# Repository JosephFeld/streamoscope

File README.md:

# Streamoscope
The Streamoscope is a USB-3 data acquisition system designed for low-field MRI, but could be more generally used. It streams two channels at 60 megasamples per second with 14-bit precision and costs around $300 in parts. It can read in data with low latency and the limit of how much can be read is only limited by the RAM on your computer!

It reads in 8 channels of data from the [AFE5812 analog front end chip](https://www.ti.com/product/AFE5812) into an [Alchitry Au FPGA board](https://www.sparkfun.com/products/16527), which feeds it into an [FT601 FIFO-to-USB-3 Bridge](https://ftdichip.com/products/ft601q-b/) which can be read into [Python](https://www.python.org/). Due to bandwidth constraints of the FT601, it only streams two channels. However, more could be streamed with a modified FPGA design that decimates the signals or decreases their precision.

What follows are guides on how to access the various components of the system. To summarize them:

* PCB design files from KiCad
* Python code for reading in data from the FT601
* Teensy code for configuring the AFE5812
* How to configure the Alchitry Au FPGA
* A Vivado project for the FPGA design

# PCB

The PCB design was done in [KiCad 8.0](https://www.kicad.org/) and can be found in ```streamoscope/hardware/kicad_design```. There are custom footprints used, which are accessible in this [library](https://github.com/JosephFeld/Handheld-MRI-Parts). Special thanks to [Lopfi for making the Alchitry Au footprint](https://github.com/Lopfi/alchitry-element-kicad).

# Python Setup

Streamoscope data can be read into Python, and this guide will walk through setting up the Jupyter Notebook example. This uses Python 3, which can be downloaded [here](https://www.python.org/downloads/).

## Installing libusb

First, we need to install [libusb](https://libusb.info/).

### MacOS

On MacOS, run these commands in the terminal: 
```
brew install libusb
sudo ln -s /opt/homebrew/lib/libusb-1.0.0.dylib /usr/local/lib/libusb.dylib
```

### Windows

On Windows, download the latest libusb Windows binaries [here](https://libusb.info/) under Downloads>Latest Windows Binaries.

Unzip the file and choose a version corresponding to your operating system. A good default is the newest Visual Studio folder VS2022. Choose the subfolder corresponding to your operating system, either 32 or 64 for 32-bit or 64-bit systems, respectively. Copy ```libusb-1.0.dll``` in the ```dll``` folder into ```C:/Windows/System32```, which will require admin approval. ```libusb-1.0.dll``` can also be placed into the same directory as the python script, ```streamoscope/software/python_reading``` for this example.

The FT601 on the Streamoscope may have the incorrect drivers. To fix this, install [Zadig](https://zadig.akeo.ie/) and run it.

* Select Options\>List All Devices
* Select FTDI SuperSpeed-FIFO Bridge (Interface 0)
* Use the arrows on the right to select libusbK as the new driver.

Here's what it should look like:

* Click "Replace Driver"

## Python dependencies

Then install the Python dependencies

```
pip install libusb, pyusb, matplotlib, numpy, scipy, jupyter
```

## Jupyter Notebook Setup

In the terminal, cd into ```streamoscope/software/python_reading``` and run this command to start up the Jupyter Notebook:

```jupyter notebook .\spin_echo_reader.ipynb```

# Teensy Setup

The Streamoscope uses a Teensy 4.1 microcontroller to configure the AFE5812 Analog Front End and ADC. The software for programming the Teensy can be found [here](https://www.pjrc.com/teensy/td_download.html).

To plug the Teensy into the Streamoscope, connect these pins:

| Streamoscope Pin | Teensy Pin |
| ---------------- | ---------- |
| ADC_RESET        | 3          |      
| MISO             | 39         |
| MOSI             | 26         |
| SCLK             | 27         |
| CS_AFE           | 38         |

And program the Teensy using the code in ```streamoscope\software\teensy_4_1_afe5812_config\teensy_4_1_afe5812_config.ino```. Every time the Teensy powers up, it reconfigures the AFE5812. 

# Configuring Alchitry Au

The Alchitry Au can be programmed using [Alchitry Loader](https://alchitry.com/alchitry-labs/) with the bitstreams found in ```streamoscope/fpga_configurations/```. It is also compatible with [openFPGALoader](https://github.com/trabucayre/openFPGALoader).

There is also a JTAG port broken out which can be used with JTAG programmers like [this](https://digilent.com/shop/jtag-hs3-programming-cable/), which can enable use of the Vivado ILA.

Here are descriptions of each bitstream:

| Filename | Description |
| ---------------- | ---------- |
| teensy_triggered.bit  | Streams channels 1 and 3 with data validity set by GPIO_0 (active high). This is useful for individual spin echoes. |      
| teensy_triggered_with_500ms_trigger_extension.bit | Streams channels 1 and 3 with data validity set by GPIO_0 (active high). Validity lasts an extra 500 milliseconds after GPIO_0 goes low. This is useful for fast imaging sequences. |

# Vivado Project Setup
The FPGA design was made in [Vivado 2023.2](https://www.xilinx.com/support/download/index.html/content/xilinx/en/downloadNav/vivado-design-tools/2023-2.html). It is only necessary to use this if you need to modify the HDL on the FPGA since There is already a provided FPGA configuration.

Open the Vivado GUI, go to the tcl console on the bottom, and cd into the ```streamoscope/hdl/Streamoscope/``` directory. Then run this command:

```
source Streamoscope.tcl
```

Then wait for a bit while the project configures. It will open up the new Streamoscope project. Then in the new project's tcl console, generate the modified ADC LVDS IP with these commands:

```
cd ../ADC-lvds-main/ip
source adc_lvds_ip.tcl
```

Then run this command in the Streamoscope tcl console to update the IP catalog:

```
update_ip_catalog -rebuild
```

If you're running on a version after 2023.2, you may need to update the IP versions. You can do that by navigating to Reports>Report IP Status. In the menu that pops up, select Upgrade Selected.

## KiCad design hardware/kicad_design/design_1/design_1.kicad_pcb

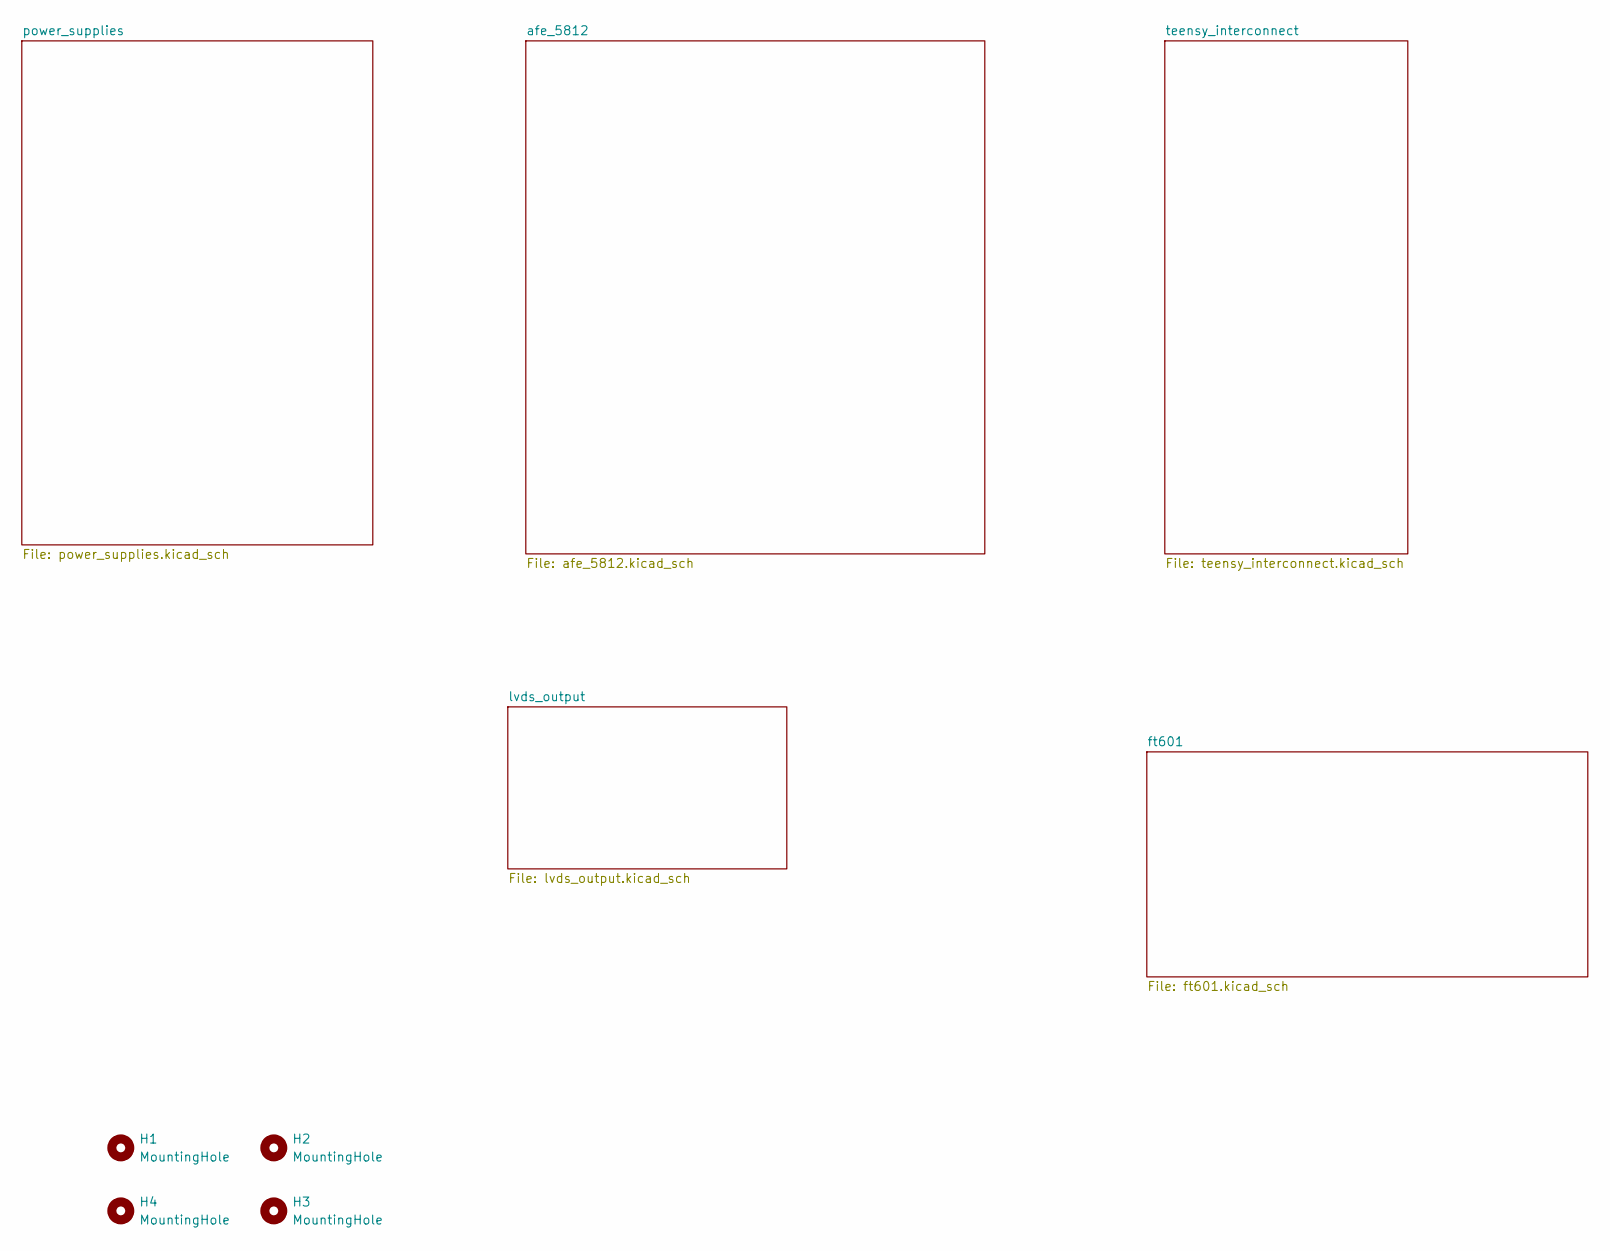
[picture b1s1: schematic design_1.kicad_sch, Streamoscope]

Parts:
H1, H2, H3, H4: MountingHole; MountingHole_2.2mm_M2

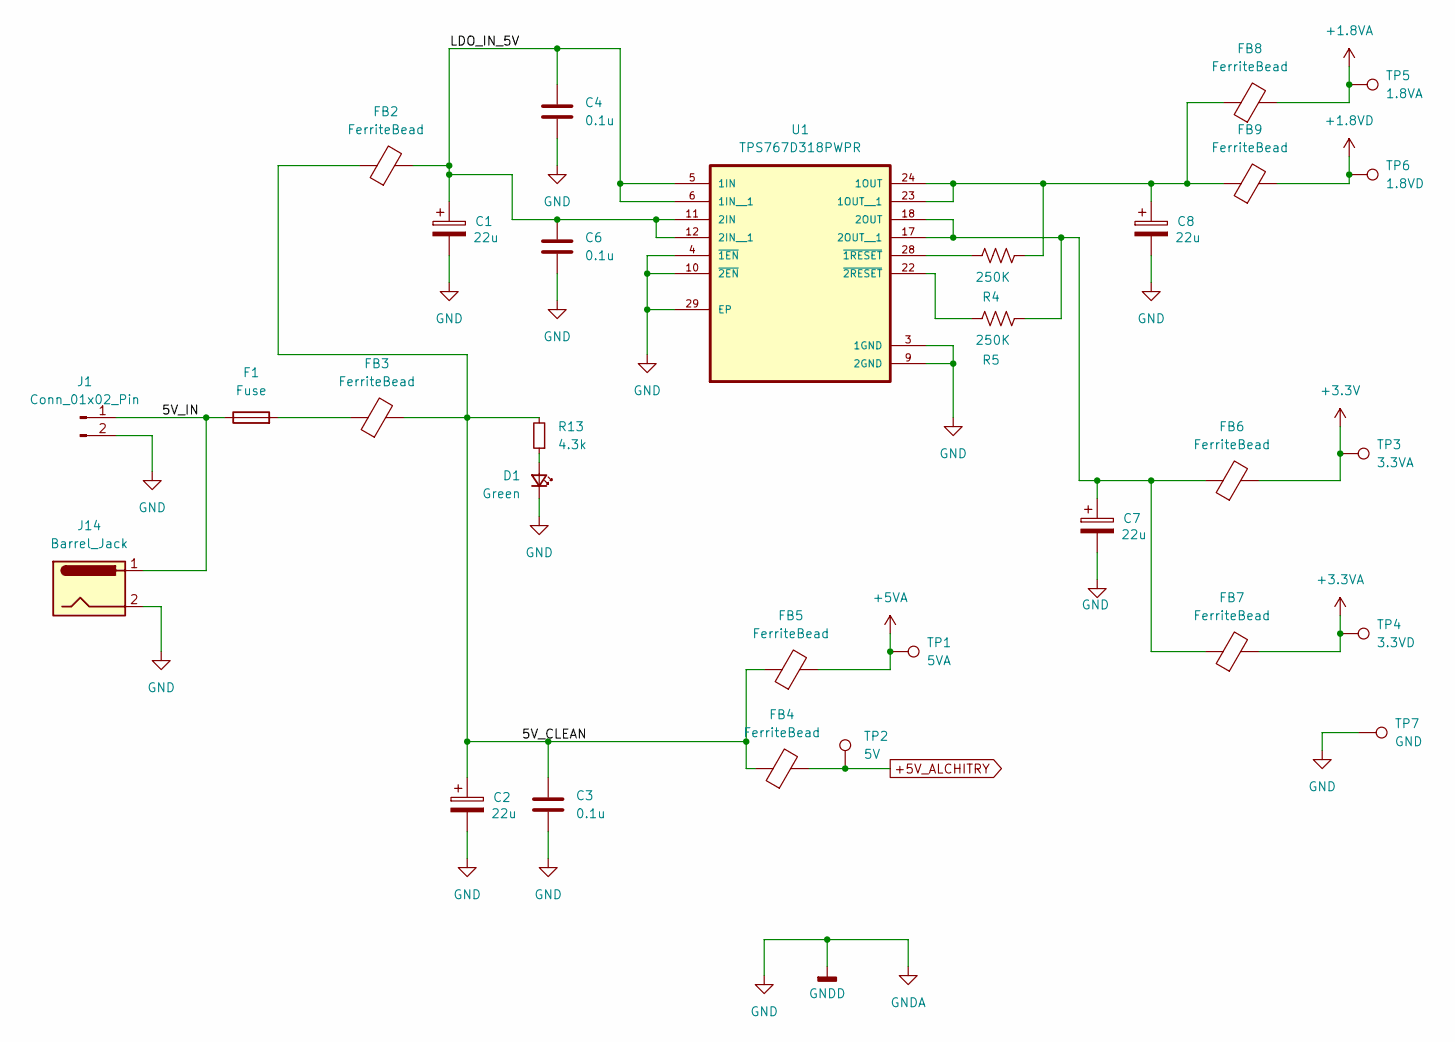
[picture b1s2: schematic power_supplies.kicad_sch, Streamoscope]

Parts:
C1, C2, C7, C8: 22u; CP_EIA-6032-20_AVX-F
C3, C4, C6: 0.1u; C_0402_1005Metric_Pad0.74x0.62mm_HandSolder
D1: Green; LED_0603_1608Metric
F1: Fuse; Fuse_0402_1005Metric_Pad0.77x0.64mm_HandSolder
FB2, FB3, FB4, FB5, FB6, FB7, FB8, FB9: FerriteBead; L_0805_2012Metric
J1: Conn_01x02_Pin; PinHeader_1x02_P2.54mm_Vertical
J14: Barrel_Jack; BarrelJack_Horizontal
R4, R5: 250K; R_0402_1005Metric_Pad0.72x0.64mm_HandSolder
R13: 4.3k; R_0402_1005Metric_Pad0.72x0.64mm_HandSolder
TP1: 5VA; TestPoint_Pad_2.0x2.0mm
TP2: 5V; TestPoint_Pad_2.0x2.0mm
TP3: 3.3VA; TestPoint_Pad_2.0x2.0mm
TP4: 3.3VD; TestPoint_Pad_2.0x2.0mm
TP5: 1.8VA; TestPoint_Pad_2.0x2.0mm
TP6: 1.8VD; TestPoint_Pad_2.0x2.0mm
TP7: GND; TestPoint_Pad_2.0x2.0mm
U1: TPS767D318PWPR; IC_TPS61196PWPRQ1

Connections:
+1.8VA: FB8.2, TP5.1; also elsewhere on the board
+1.8VD: FB9.2, TP6.1; also elsewhere on the board
+3.3V: FB6.2, TP3.1; also elsewhere on the board
+3.3VA: FB7.2, TP4.1; also elsewhere on the board
+5VA: FB5.2, TP1.1; also elsewhere on the board
+5V_ALCHITRY: FB4.2, TP2.1; also elsewhere on the board
/power_supplies/5V_CLEAN: C2.1, C3.1, FB2.1, FB3.2, FB4.1, FB5.1, R13.2
/power_supplies/5V_IN: F1.1, J1.1, J14.1
/power_supplies/LDO_IN_5V: C1.1, C4.1, C6.1, FB2.2, U1.5 (1IN), U1.6 (1IN__1), U1.11 (2IN), U1.12 (2IN__1)
GND: C1.2, C2.2, C3.2, C4.2, C6.2, C7.2, C8.2, D1.1 (K), J1.2, J14.2, TP7.1, U1.3 (1GND), U1.4 (~1EN), U1.9 (2GND), U1.10 (~2EN), U1.29 (EP); also elsewhere on the board
unnamed: D1.2 (A), R13.1
unnamed: F1.2, FB3.1
unnamed: C8.1, FB8.1, FB9.1, R4.2, U1.23 (1OUT__1), U1.24 (1OUT)
unnamed: C7.1, FB6.1, FB7.1, R5.2, U1.17 (2OUT__1), U1.18 (2OUT)
unnamed: R4.1, U1.28 (~1RESET)
unnamed: R5.1, U1.22 (~2RESET)

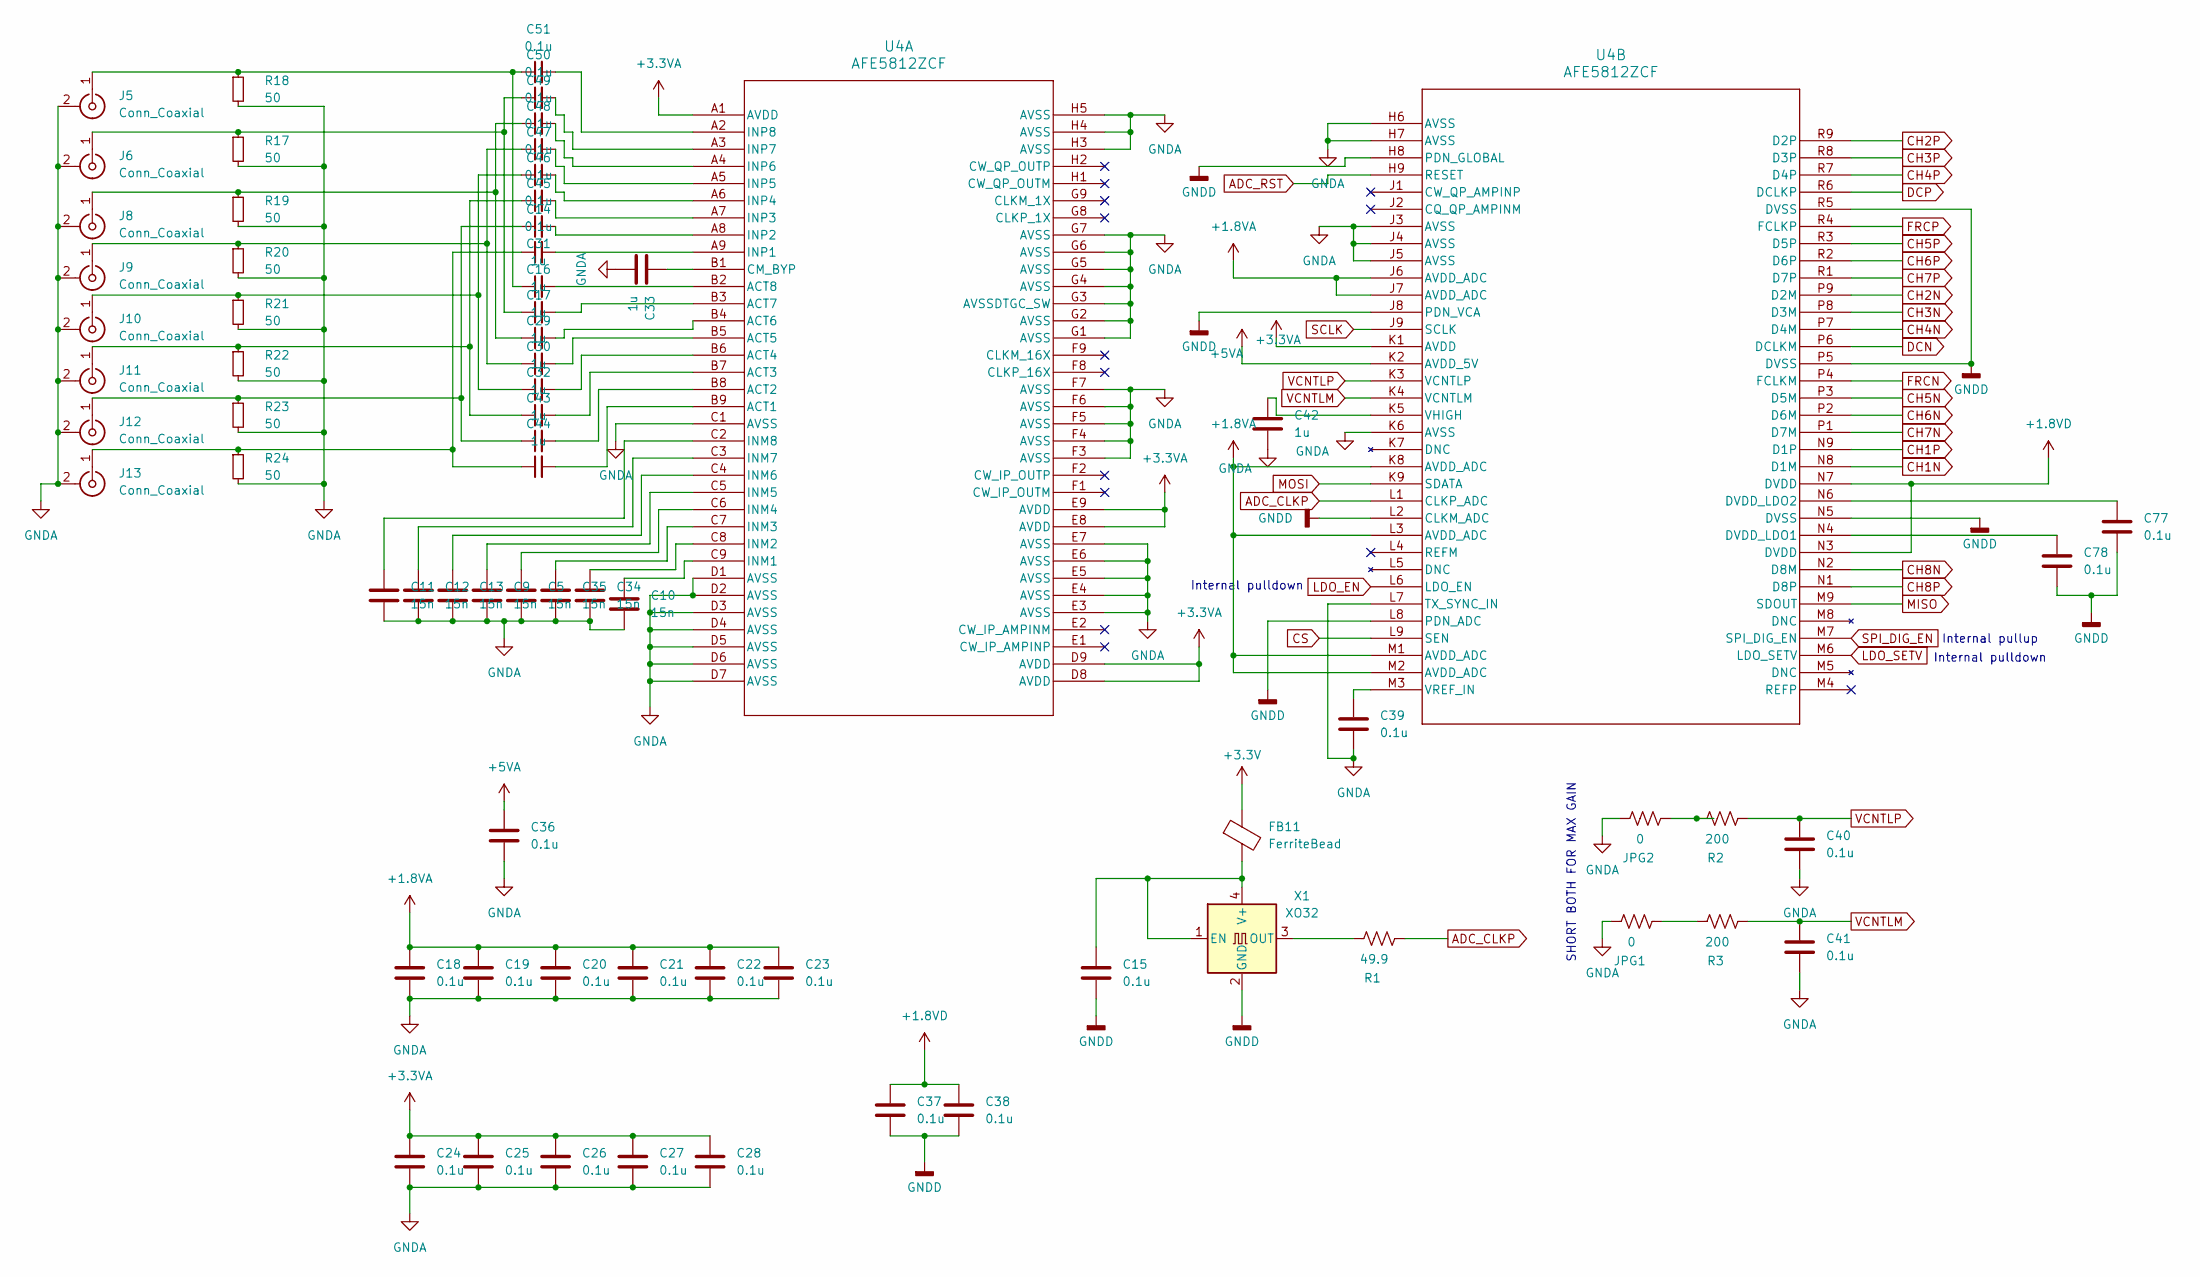
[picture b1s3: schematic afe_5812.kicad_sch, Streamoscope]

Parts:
C5, C9, C10, C11, C12, C13, C34, C35: 15n; C_0402_1005Metric_Pad0.74x0.62mm_HandSolder
C14, C15, C18, C19, C20, C21, C22, C23, C24, C25, C26, C27, C28, C36, C37, C38, C39, C40, C41, C45, C46, C47, C48, C49, C50, C51, C77, C78: 0.1u; C_0402_1005Metric_Pad0.74x0.62mm_HandSolder
C16, C17, C29, C30, C31, C32, C33, C42, C43, C44: 1u; C_0402_1005Metric_Pad0.74x0.62mm_HandSolder
FB11: FerriteBead; L_0402_1005Metric
J5, J6, J8, J9, J10, J11, J12, J13: Conn_Coaxial; SMA_Amphenol_132134_Vertical
JPG1, JPG2: 0; R_0402_1005Metric_Pad0.72x0.64mm_HandSolder
R1: 49.9; R_0402_1005Metric_Pad0.72x0.64mm_HandSolder
R2, R3: 200; R_0402_1005Metric_Pad0.72x0.64mm_HandSolder
R17, R18, R19, R20, R21, R22, R23, R24: 50; R_0402_1005Metric
U4: AFE5812ZCF; ZCF135_TEX_NO_PASTE
X1: XO32; Oscillator_SMD_Abracon_ASV-4Pin_7.0x5.1mm

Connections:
+1.8VA: C18.1, C19.1, C20.1, C21.1, C22.1, C23.1, U4.J6 (AVDD_ADC), U4.J7 (AVDD_ADC), U4.K8 (AVDD_ADC), U4.L3 (AVDD_ADC), U4.M1 (AVDD_ADC), U4.M2 (AVDD_ADC); also elsewhere on the board
+1.8VD: C37.1, C38.1, U4.N3 (DVDD), U4.N7 (DVDD); also elsewhere on the board
+3.3V: FB11.1; also elsewhere on the board
+3.3VA: C24.1, C25.1, C26.1, C27.1, C28.1, U4.A1 (AVDD), U4.D8 (AVDD), U4.D9 (AVDD), U4.E8 (AVDD), U4.E9 (AVDD), U4.K1 (AVDD); also elsewhere on the board
+5VA: C36.1, U4.K2 (AVDD_5V); also elsewhere on the board
ADC_CLKP: R1.2, U4.L1 (CLKP_ADC)
ADC_RST: U4.H9 (RESET); also elsewhere on the board
CH1N: U4.N8 (D1M); also elsewhere on the board
CH1P: U4.N9 (D1P); also elsewhere on the board
CH2N: U4.P9 (D2M); also elsewhere on the board
CH2P: U4.R9 (D2P); also elsewhere on the board
CH3N: U4.P8 (D3M); also elsewhere on the board
CH3P: U4.R8 (D3P); also elsewhere on the board
CH4N: U4.P7 (D4M); also elsewhere on the board
CH4P: U4.R7 (D4P); also elsewhere on the board
CH5N: U4.P3 (D5M); also elsewhere on the board
CH5P: U4.R3 (D5P); also elsewhere on the board
CH6N: U4.P2 (D6M); also elsewhere on the board
CH6P: U4.R2 (D6P); also elsewhere on the board
CH7N: U4.P1 (D7M); also elsewhere on the board
CH7P: U4.R1 (D7P); also elsewhere on the board
CH8N: U4.N2 (D8M); also elsewhere on the board
CH8P: U4.N1 (D8P); also elsewhere on the board
CS: U4.L9 (SEN); also elsewhere on the board
DCN: U4.P6 (DCLKM); also elsewhere on the board
DCP: U4.R6 (DCLKP); also elsewhere on the board
FRCN: U4.P4 (FCLKM); also elsewhere on the board
FRCP: U4.R4 (FCLKP); also elsewhere on the board
GND: C5.1, C9.1, C10.1, C11.1, C12.1, C13.1, C15.2, C18.2, C19.2, C20.2, C21.2, C22.2, C23.2, C24.2, C25.2, C26.2, C27.2, C28.2, C33.1, C34.1, C35.1, C36.2, C37.2, C38.2, C39.2, C40.2, C41.2, C42.1, C77.2, C78.2, J5.2 (Ext), J6.2 (Ext), J8.2 (Ext), J9.2 (Ext), J10.2 (Ext), J11.2 (Ext), J12.2 (Ext), J13.2 (Ext), JPG1.1, JPG2.1, R17.2, R18.2, R19.2, R20.2, R21.2, R22.2, R23.2, R24.2, U4.C1 (AVSS), U4.D1 (AVSS), U4.D2 (AVSS), U4.D3 (AVSS), U4.D4 (AVSS), U4.D5 (AVSS), U4.D6 (AVSS), U4.D7 (AVSS), U4.E3 (AVSS), U4.E4 (AVSS), U4.E5 (AVSS), U4.E6 (AVSS), U4.E7 (AVSS), U4.F3 (AVSS), U4.F4 (AVSS), U4.F5 (AVSS), U4.F6 (AVSS), U4.F7 (AVSS), U4.G1 (AVSS), U4.G2 (AVSS), U4.G3 (AVSSDTGC_SW), U4.G4 (AVSS), U4.G5 (AVSS), U4.G6 (AVSS), U4.G7 (AVSS), U4.H3 (AVSS), U4.H4 (AVSS), U4.H5 (AVSS), U4.H6 (AVSS), U4.H7 (AVSS), U4.H8 (PDN_GLOBAL), U4.J3 (AVSS), U4.J4 (AVSS), U4.J5 (AVSS), U4.J8 (PDN_VCA), U4.K6 (AVSS), U4.L2 (CLKM_ADC), U4.L7 (TX_SYNC_IN), U4.L8 (PDN_ADC), U4.N5 (DVSS), U4.P5 (DVSS), U4.R5 (DVSS), X1.2 (GND); also elsewhere on the board
LDO_EN: U4.L6 (LDO_EN); also elsewhere on the board
LDO_SETV: U4.M6 (LDO_SETV); also elsewhere on the board
MISO: U4.M9 (SDOUT); also elsewhere on the board
MOSI: U4.K9 (SDATA); also elsewhere on the board
unnamed: C31.1, C51.1, J5.1 (In), R18.1
unnamed: C16.1, C50.1, J6.1 (In), R17.1
unnamed: C17.1, C49.1, J8.1 (In), R19.1
unnamed: C29.1, C48.1, J9.1 (In), R20.1
unnamed: C30.1, C47.1, J10.1 (In), R21.1
unnamed: C32.1, C46.1, J11.1 (In), R22.1
unnamed: C43.1, C45.1, J12.1 (In), R23.1
unnamed: C14.1, C44.1, J13.1 (In), R24.1
unnamed: JPG1.2, R3.1
unnamed: JPG2.2, R2.1
unnamed: C44.2, U4.B9 (ACT1)
unnamed: C43.2, U4.B8 (ACT2)
unnamed: C32.2, U4.B7 (ACT3)
unnamed: C30.2, U4.B6 (ACT4)
unnamed: C29.2, U4.B5 (ACT5)
unnamed: C17.2, U4.B4 (ACT6)
unnamed: C16.2, U4.B3 (ACT7)
unnamed: C31.2, U4.B2 (ACT8)
unnamed: C33.2, U4.B1 (CM_BYP)
unnamed: C10.2, U4.C9 (INM1)
unnamed: C34.2, U4.C8 (INM2)
unnamed: C35.2, U4.C7 (INM3)
unnamed: C5.2, U4.C6 (INM4)
unnamed: C9.2, U4.C5 (INM5)
unnamed: C13.2, U4.C4 (INM6)
unnamed: C12.2, U4.C3 (INM7)
unnamed: C11.2, U4.C2 (INM8)
unnamed: C14.2, U4.A9 (INP1)
unnamed: C45.2, U4.A8 (INP2)
unnamed: C46.2, U4.A7 (INP3)
unnamed: C47.2, U4.A6 (INP4)
unnamed: C48.2, U4.A5 (INP5)
unnamed: C49.2, U4.A4 (INP6)
unnamed: C50.2, U4.A3 (INP7)
unnamed: C51.2, U4.A2 (INP8)
unnamed: C78.1, U4.N4 (DVDD_LDO1)
unnamed: C77.1, U4.N6 (DVDD_LDO2)
unnamed: C42.2, U4.K5 (VHIGH)
unnamed: C39.1, U4.M3 (VREF_IN)
unnamed: C15.1, FB11.2, X1.1 (EN), X1.4 (V+)
unnamed: R1.1, X1.3 (OUT)
SCLK: U4.J9 (SCLK); also elsewhere on the board
SPI_DIG_EN: U4.M7 (SPI_DIG_EN); also elsewhere on the board
VCNTLM: C41.1, R3.2, U4.K4 (VCNTLM)
VCNTLP: C40.1, R2.2, U4.K3 (VCNTLP)

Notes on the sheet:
Internal pullup
Internal pulldown
SHORT BOTH FOR MAX GAIN

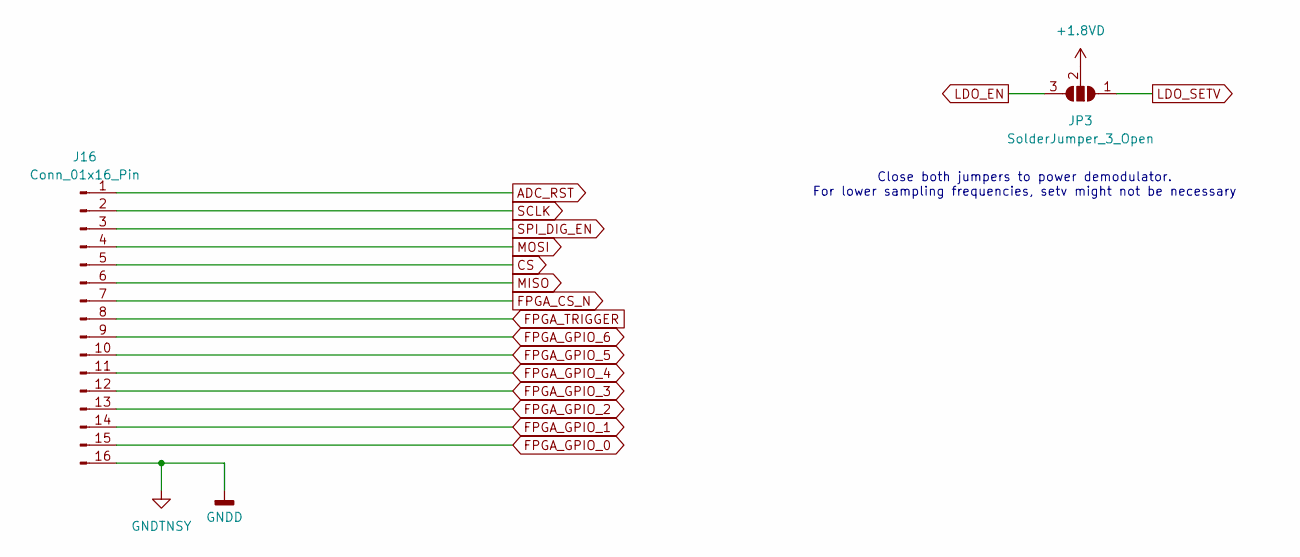
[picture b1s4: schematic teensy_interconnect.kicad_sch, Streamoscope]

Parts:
J16: Conn_01x16_Pin; PinHeader_1x16_P2.54mm_Vertical
JP3: SolderJumper_3_Open; SolderJumper-3_P1.3mm_Open_Pad1.0x1.5mm

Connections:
+1.8VD: JP3.2 (C); also elsewhere on the board
ADC_RST: J16.1; also elsewhere on the board
CS: J16.5; also elsewhere on the board
FPGA_CS_N: J16.7; also elsewhere on the board
FPGA_GPIO_0: J16.15; also elsewhere on the board
FPGA_GPIO_1: J16.14; also elsewhere on the board
FPGA_GPIO_2: J16.13; also elsewhere on the board
FPGA_GPIO_3: J16.12; also elsewhere on the board
FPGA_GPIO_4: J16.11; also elsewhere on the board
FPGA_GPIO_5: J16.10; also elsewhere on the board
FPGA_GPIO_6: J16.9; also elsewhere on the board
FPGA_TRIGGER: J16.8; also elsewhere on the board
GND: J16.16; also elsewhere on the board
LDO_EN: JP3.3 (B); also elsewhere on the board
LDO_SETV: JP3.1 (A); also elsewhere on the board
MISO: J16.6; also elsewhere on the board
MOSI: J16.4; also elsewhere on the board
SCLK: J16.2; also elsewhere on the board
SPI_DIG_EN: J16.3; also elsewhere on the board

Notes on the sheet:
Close both jumpers to power demodulator. For lower sampling frequencies, setv might not be necessary

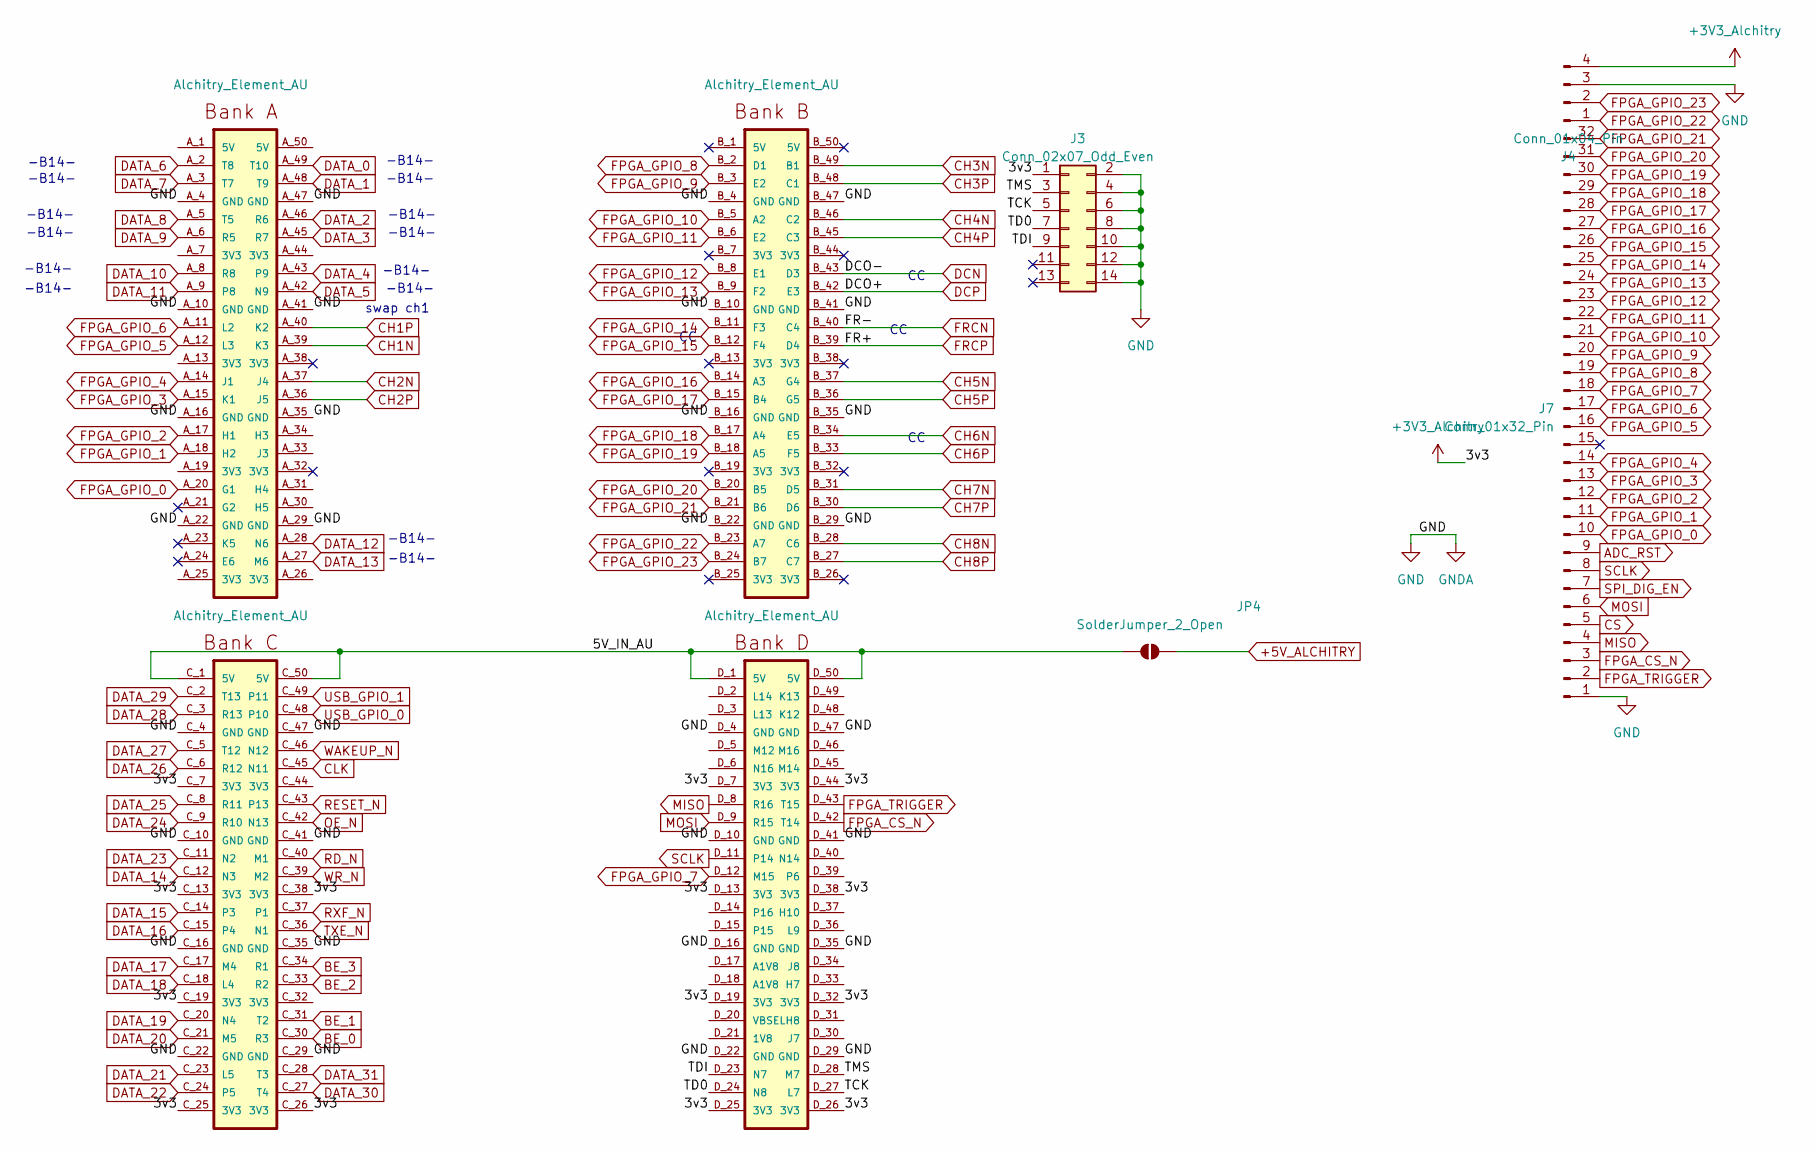
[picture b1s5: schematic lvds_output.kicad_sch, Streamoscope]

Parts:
B1: Alchitry_Element_AU; Element_no_top
J3: Conn_02x07_Odd_Even; PinSocket_2x07_P2.00mm_Vertical
J4: Conn_01x04_Pin; PinSocket_1x04_P2.54mm_Vertical
J7: Conn_01x32_Pin; PinHeader_1x32_P2.54mm_Vertical
JP4: SolderJumper_2_Open; SolderJumper-2_P1.3mm_Open_Pad1.0x1.5mm

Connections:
+3V3_Alchitry: B1.C_7 (3V3), B1.C_13 (3V3), B1.C_19 (3V3), B1.C_25 (3V3), B1.C_26 (3V3), B1.C_38 (3V3), B1.D_7 (3V3), B1.D_13 (3V3), B1.D_19 (3V3), B1.D_25 (3V3), B1.D_26 (3V3), B1.D_32 (3V3), B1.D_38 (3V3), B1.D_44 (3V3), J3.1, J4.4; also elsewhere on the board
+5V_ALCHITRY: JP4.2 (B); also elsewhere on the board
/lvds_output/5V_IN_AU: B1.C_1 (5V), B1.C_50 (5V), B1.D_1 (5V), B1.D_50 (5V), JP4.1 (A)
/lvds_output/TCK: B1.D_27 (L7), J3.5
/lvds_output/TD0: B1.D_24 (N8), J3.7
/lvds_output/TDI: B1.D_23 (N7), J3.9
/lvds_output/TMS: B1.D_28 (M7), J3.3
ADC_RST: J7.9; also elsewhere on the board
BE_0: B1.C_30 (R3); also elsewhere on the board
BE_1: B1.C_31 (T2); also elsewhere on the board
BE_2: B1.C_33 (R2); also elsewhere on the board
BE_3: B1.C_34 (R1); also elsewhere on the board
CH1N: B1.A_39 (K3); also elsewhere on the board
CH1P: B1.A_40 (K2); also elsewhere on the board
CH2N: B1.A_37 (J4); also elsewhere on the board
CH2P: B1.A_36 (J5); also elsewhere on the board
CH3N: B1.B_49 (B1); also elsewhere on the board
CH3P: B1.B_48 (C1); also elsewhere on the board
CH4N: B1.B_46 (C2); also elsewhere on the board
CH4P: B1.B_45 (C3); also elsewhere on the board
CH5N: B1.B_37 (G4); also elsewhere on the board
CH5P: B1.B_36 (G5); also elsewhere on the board
CH6N: B1.B_34 (E5); also elsewhere on the board
CH6P: B1.B_33 (F5); also elsewhere on the board
CH7N: B1.B_31 (D5); also elsewhere on the board
CH7P: B1.B_30 (D6); also elsewhere on the board
CH8N: B1.B_28 (C6); also elsewhere on the board
CH8P: B1.B_27 (C7); also elsewhere on the board
CLK: B1.C_45 (N11); also elsewhere on the board
CS: J7.5; also elsewhere on the board
DATA_0: B1.A_49 (T10); also elsewhere on the board
DATA_1: B1.A_48 (T9); also elsewhere on the board
DATA_2: B1.A_46 (R6); also elsewhere on the board
DATA_3: B1.A_45 (R7); also elsewhere on the board
DATA_4: B1.A_43 (P9); also elsewhere on the board
DATA_5: B1.A_42 (N9); also elsewhere on the board
DATA_6: B1.A_2 (T8); also elsewhere on the board
DATA_7: B1.A_3 (T7); also elsewhere on the board
DATA_8: B1.A_5 (T5); also elsewhere on the board
DATA_9: B1.A_6 (R5); also elsewhere on the board
DATA_10: B1.A_8 (R8); also elsewhere on the board
DATA_11: B1.A_9 (P8); also elsewhere on the board
DATA_12: B1.A_28 (N6); also elsewhere on the board
DATA_13: B1.A_27 (M6); also elsewhere on the board
DATA_14: B1.C_12 (N3); also elsewhere on the board
DATA_15: B1.C_14 (P3); also elsewhere on the board
DATA_16: B1.C_15 (P4); also elsewhere on the board
DATA_17: B1.C_17 (M4); also elsewhere on the board
DATA_18: B1.C_18 (L4); also elsewhere on the board
DATA_19: B1.C_20 (N4); also elsewhere on the board
DATA_20: B1.C_21 (M5); also elsewhere on the board
DATA_21: B1.C_23 (L5); also elsewhere on the board
DATA_22: B1.C_24 (P5); also elsewhere on the board
DATA_23: B1.C_11 (N2); also elsewhere on the board
DATA_24: B1.C_9 (R10); also elsewhere on the board
DATA_25: B1.C_8 (R11); also elsewhere on the board
DATA_26: B1.C_6 (R12); also elsewhere on the board
DATA_27: B1.C_5 (T12); also elsewhere on the board
DATA_28: B1.C_3 (R13); also elsewhere on the board
DATA_29: B1.C_2 (T13); also elsewhere on the board
DATA_30: B1.C_27 (T4); also elsewhere on the board
DATA_31: B1.C_28 (T3); also elsewhere on the board
DCN: B1.B_43 (D3); also elsewhere on the board
DCP: B1.B_42 (E3); also elsewhere on the board
FPGA_CS_N: B1.D_42 (T14), J7.3; also elsewhere on the board
FPGA_GPIO_0: B1.A_20 (G1), J7.10; also elsewhere on the board
FPGA_GPIO_1: B1.A_18 (H2), J7.11; also elsewhere on the board
FPGA_GPIO_2: B1.A_17 (H1), J7.12; also elsewhere on the board
FPGA_GPIO_3: B1.A_15 (K1), J7.13; also elsewhere on the board
FPGA_GPIO_4: B1.A_14 (J1), J7.14; also elsewhere on the board
FPGA_GPIO_5: B1.A_12 (L3), J7.16; also elsewhere on the board
FPGA_GPIO_6: B1.A_11 (L2), J7.17; also elsewhere on the board
FPGA_GPIO_7: B1.D_12 (M15), J7.18
FPGA_GPIO_8: B1.B_2 (D1), J7.19
FPGA_GPIO_9: B1.B_3 (E2), J7.20
FPGA_GPIO_10: B1.B_5 (A2), J7.21
FPGA_GPIO_11: B1.B_6 (E2), J7.22
FPGA_GPIO_12: B1.B_8 (E1), J7.23
FPGA_GPIO_13: B1.B_9 (F2), J7.24
FPGA_GPIO_14: B1.B_11 (F3), J7.25
FPGA_GPIO_15: B1.B_12 (F4), J7.26
FPGA_GPIO_16: B1.B_14 (A3), J7.27
FPGA_GPIO_17: B1.B_15 (B4), J7.28
FPGA_GPIO_18: B1.B_17 (A4), J7.29
FPGA_GPIO_19: B1.B_18 (A5), J7.30
FPGA_GPIO_20: B1.B_20 (B5), J7.31
FPGA_GPIO_21: B1.B_21 (B6), J7.32
FPGA_GPIO_22: B1.B_23 (A7), J4.1
FPGA_GPIO_23: B1.B_24 (B7), J4.2
FPGA_TRIGGER: B1.D_43 (T15), J7.2; also elsewhere on the board
FRCN: B1.B_40 (C4); also elsewhere on the board
FRCP: B1.B_39 (D4); also elsewhere on the board
GND: B1.A_4 (GND), B1.A_10 (GND), B1.A_16 (GND), B1.A_22 (GND), B1.A_29 (GND), B1.A_35 (GND), B1.A_41 (GND), B1.A_47 (GND), B1.B_4 (GND), B1.B_10 (GND), B1.B_16 (GND), B1.B_22 (GND), B1.B_29 (GND), B1.B_35 (GND), B1.B_41 (GND), B1.B_47 (GND), B1.C_4 (GND), B1.C_10 (GND), B1.C_16 (GND), B1.C_22 (GND), B1.C_29 (GND), B1.C_35 (GND), B1.C_41 (GND), B1.C_47 (GND), B1.D_4 (GND), B1.D_10 (GND), B1.D_16 (GND), B1.D_22 (GND), B1.D_29 (GND), B1.D_35 (GND), B1.D_41 (GND), B1.D_47 (GND), J3.2, J3.4, J3.6, J3.8, J3.10, J3.12, J3.14, J4.3, J7.1; also elsewhere on the board
MISO: B1.D_8 (R16), J7.4; also elsewhere on the board
MOSI: B1.D_9 (R15), J7.6; also elsewhere on the board
OE_N: B1.C_42 (N13); also elsewhere on the board
RD_N: B1.C_40 (M1); also elsewhere on the board
RESET_N: B1.C_43 (P13); also elsewhere on the board
RXF_N: B1.C_37 (P1); also elsewhere on the board
SCLK: B1.D_11 (P14), J7.8; also elsewhere on the board
SPI_DIG_EN: J7.7; also elsewhere on the board
TXE_N: B1.C_36 (N1); also elsewhere on the board
USB_GPIO_0: B1.C_48 (P10); also elsewhere on the board
USB_GPIO_1: B1.C_49 (P11); also elsewhere on the board
WAKEUP_N: B1.C_46 (N12); also elsewhere on the board
WR_N: B1.C_39 (M2); also elsewhere on the board

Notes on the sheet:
-B14-
swap ch1
